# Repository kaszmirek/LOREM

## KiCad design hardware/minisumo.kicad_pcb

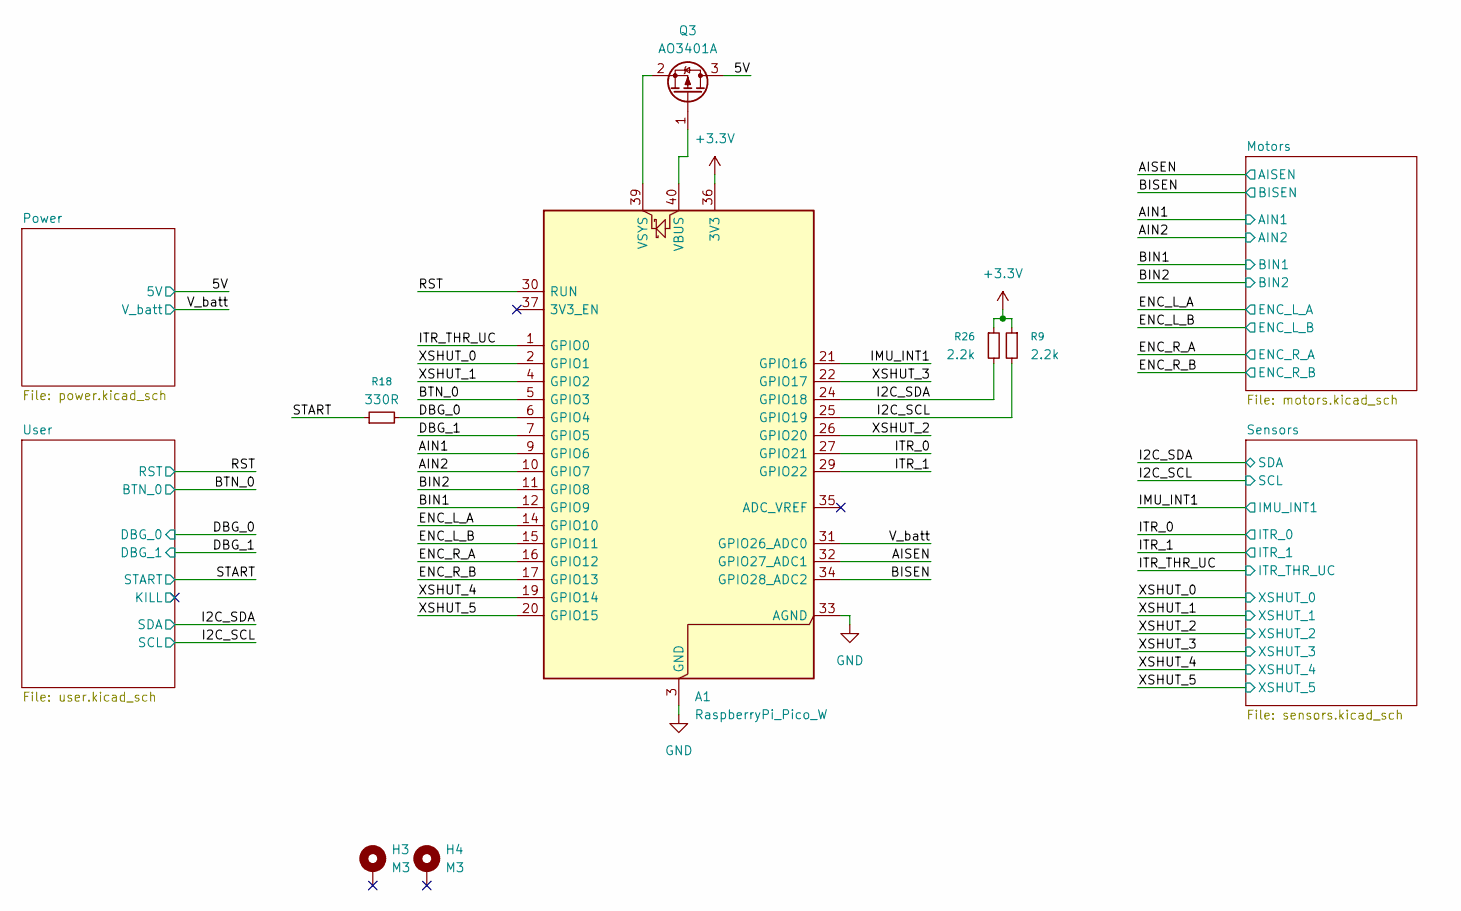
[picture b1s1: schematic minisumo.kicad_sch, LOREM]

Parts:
A1: RaspberryPi_Pico_W; RaspberryPi_Pico_W_SMD_HandSolder
H3, H4: M3; MountingHole_3.2mm_M3_Pad_Via
Q3: AO3401A; SOT-23
R9, R26: 2.2k; R_0402_1005Metric
R18: 330R; R_0402_1005Metric

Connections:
+3.3V: A1.36 (3V3), R9.1, R26.1; also elsewhere on the board
+5V: Q3.3 (D); also elsewhere on the board
/AIN1: A1.9 (GPIO6); also elsewhere on the board
/AIN2: A1.10 (GPIO7); also elsewhere on the board
/AISEN: A1.32 (GPIO27_ADC1); also elsewhere on the board
/BIN1: A1.12 (GPIO9); also elsewhere on the board
/BIN2: A1.11 (GPIO8); also elsewhere on the board
/BISEN: A1.34 (GPIO28_ADC2); also elsewhere on the board
/BTN_0: A1.5 (GPIO3); also elsewhere on the board
/DBG_0: A1.6 (GPIO4), R18.2; also elsewhere on the board
/DBG_1: A1.7 (GPIO5); also elsewhere on the board
/ENC_L_A: A1.14 (GPIO10); also elsewhere on the board
/ENC_L_B: A1.15 (GPIO11); also elsewhere on the board
/ENC_R_A: A1.16 (GPIO12); also elsewhere on the board
/ENC_R_B: A1.17 (GPIO13); also elsewhere on the board
/I2C_SCL: A1.25 (GPIO19), R9.2; also elsewhere on the board
/I2C_SDA: A1.24 (GPIO18), R26.2; also elsewhere on the board
/IMU_INT1: A1.21 (GPIO16); also elsewhere on the board
/ITR_0: A1.27 (GPIO21); also elsewhere on the board
/ITR_1: A1.29 (GPIO22); also elsewhere on the board
/ITR_THR_UC: A1.1 (GPIO0); also elsewhere on the board
/RST: A1.30 (RUN); also elsewhere on the board
/START: R18.1; also elsewhere on the board
/V_batt: A1.31 (GPIO26_ADC0); also elsewhere on the board
/XSHUT_0: A1.2 (GPIO1); also elsewhere on the board
/XSHUT_1: A1.4 (GPIO2); also elsewhere on the board
/XSHUT_2: A1.26 (GPIO20); also elsewhere on the board
/XSHUT_3: A1.22 (GPIO17); also elsewhere on the board
/XSHUT_4: A1.19 (GPIO14); also elsewhere on the board
/XSHUT_5: A1.20 (GPIO15); also elsewhere on the board
GND: A1.3 (GND), A1.8 (GND), A1.13 (GND), A1.18 (GND), A1.23 (GND), A1.28 (GND), A1.33 (AGND), A1.38 (GND); also elsewhere on the board
unnamed: A1.40 (VBUS), Q3.1 (G)
unnamed: A1.39 (VSYS), Q3.2 (S)

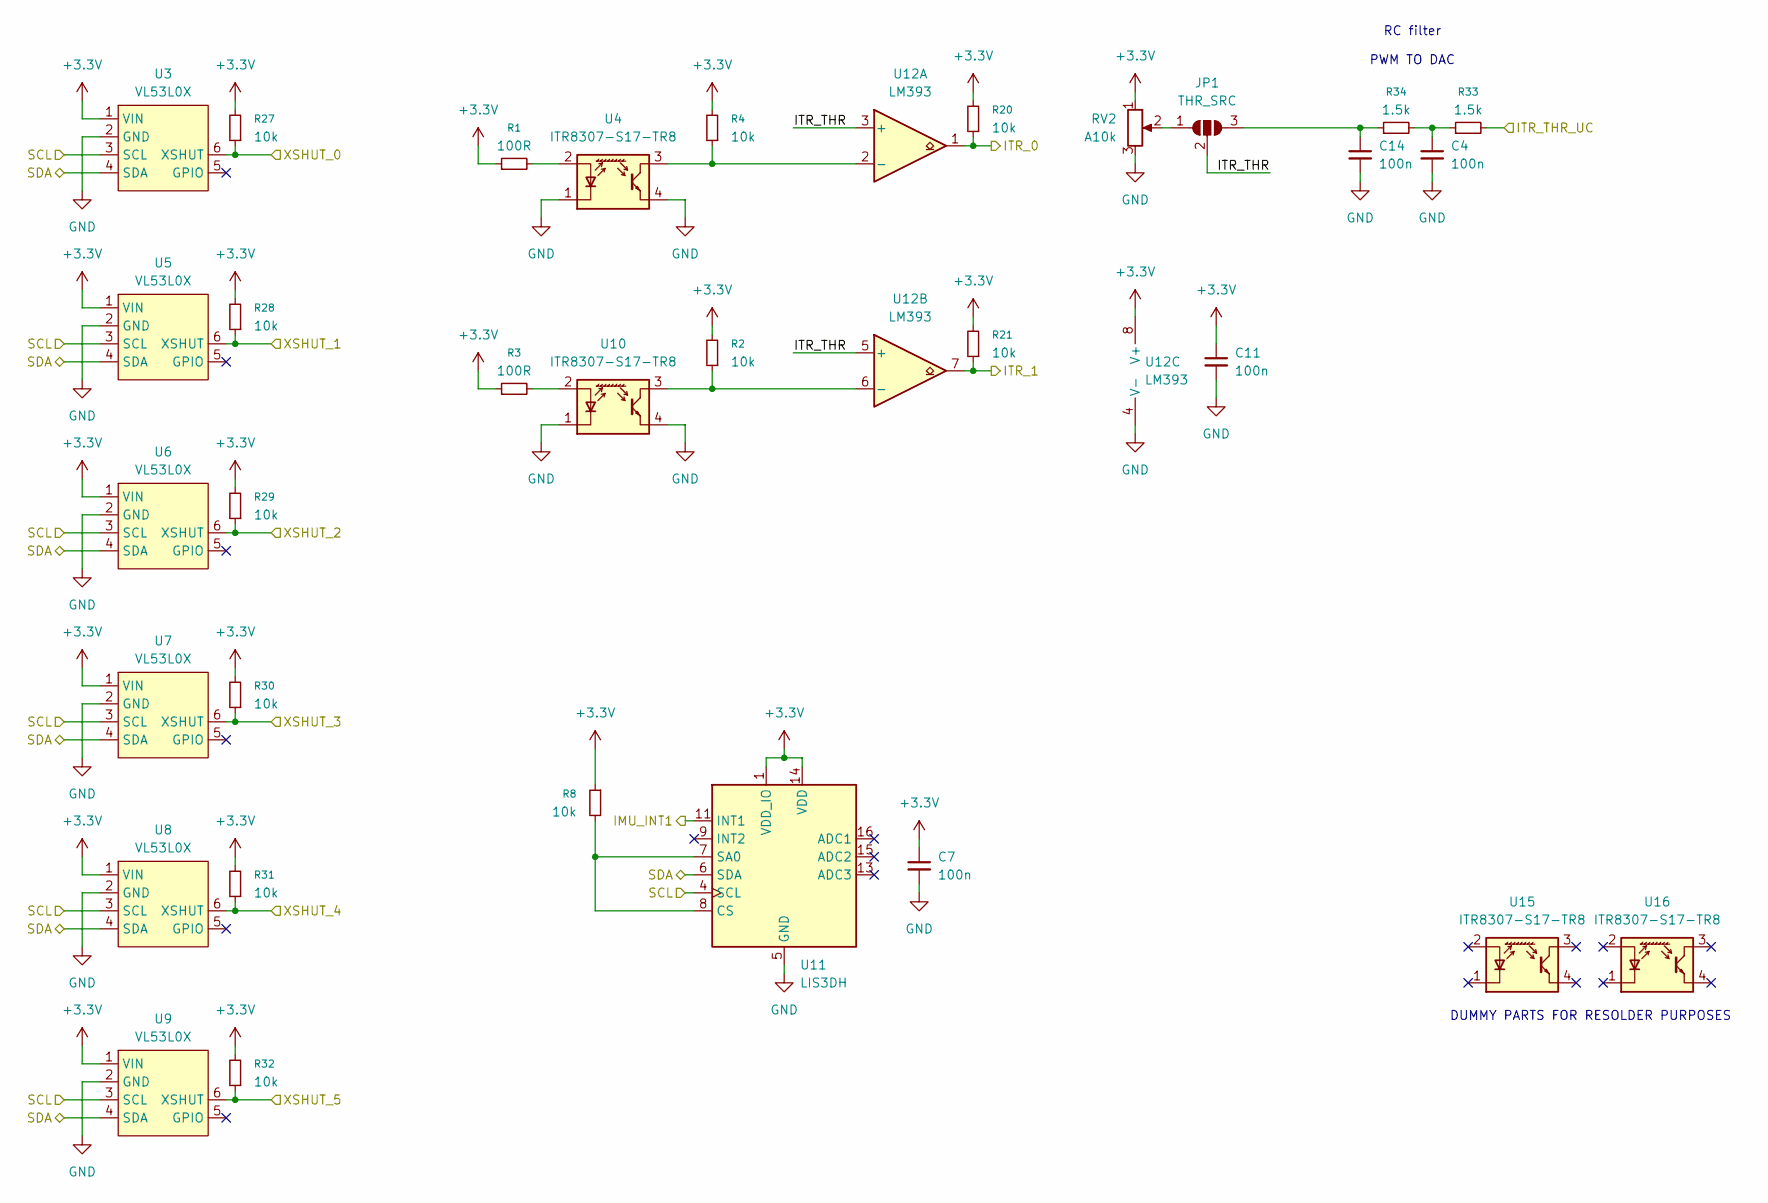
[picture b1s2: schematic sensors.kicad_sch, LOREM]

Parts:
C4, C7, C11, C14: 100n; C_0402_1005Metric
JP1: THR_SRC; SolderJumper-3_P1.3mm_Open_RoundedPad1.0x1.5mm_NumberLabels
R1, R3: 100R; R_0402_1005Metric
R2, R4, R8, R20, R21, R27, R28, R29, R30, R31, R32: 10k; R_0402_1005Metric
R33, R34: 1.5k; R_0402_1005Metric
RV2: A10k; Potentiometer_Vishay_T93YA_Vertical
U3, U5, U6, U7, U8, U9: VL53L0X
U4, U10, U15, U16: ITR8307-S17-TR8; Everlight_ITR1201SR10AR
U11: LIS3DH; LGA-16_3x3mm_P0.5mm_LayoutBorder3x5y
U12: LM393; SOIC-8_3.9x4.9mm_P1.27mm

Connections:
+3.3V: C7.1, C11.1, R1.1, R2.2, R3.1, R4.2, R8.1, R20.2, R21.2, R27.2, R28.2, R29.2, R30.2, R31.2, R32.2, RV2.1, U3.1 (VIN), U5.1 (VIN), U6.1 (VIN), U7.1 (VIN), U8.1 (VIN), U9.1 (VIN), U11.1 (VDD_IO), U11.14 (VDD), U12.8 (V+); also elsewhere on the board
/I2C_SCL: U3.3 (SCL), U5.3 (SCL), U6.3 (SCL), U7.3 (SCL), U8.3 (SCL), U9.3 (SCL), U11.4 (SCL); also elsewhere on the board
/I2C_SDA: U3.4 (SDA), U5.4 (SDA), U6.4 (SDA), U7.4 (SDA), U8.4 (SDA), U9.4 (SDA), U11.6 (SDA); also elsewhere on the board
/IMU_INT1: U11.11 (INT1); also elsewhere on the board
/ITR_0: R20.1, U12.1; also elsewhere on the board
/ITR_1: R21.1, U12.7; also elsewhere on the board
/ITR_THR_UC: R33.2; also elsewhere on the board
/Sensors/ITR_THR: JP1.2 (C), U12.3 (+), U12.5 (+)
/XSHUT_0: R27.1, U3.6 (XSHUT); also elsewhere on the board
/XSHUT_1: R28.1, U5.6 (XSHUT); also elsewhere on the board
/XSHUT_2: R29.1, U6.6 (XSHUT); also elsewhere on the board
/XSHUT_3: R30.1, U7.6 (XSHUT); also elsewhere on the board
/XSHUT_4: R31.1, U8.6 (XSHUT); also elsewhere on the board
/XSHUT_5: R32.1, U9.6 (XSHUT); also elsewhere on the board
GND: C4.2, C7.2, C11.2, C14.2, RV2.3, U3.2 (GND), U4.1 (K), U4.4, U5.2 (GND), U6.2 (GND), U7.2 (GND), U8.2 (GND), U9.2 (GND), U10.1 (K), U10.4, U11.5 (GND), U11.10 (GND), U11.12 (GND), U12.4 (V-); also elsewhere on the board
unnamed: C4.1, R33.1, R34.2
unnamed: JP1.1 (A), RV2.2
unnamed: C14.1, JP1.3 (B), R34.1
unnamed: R1.2, U4.2 (A)
unnamed: R3.2, U10.2 (A)
unnamed: R8.2, U11.7 (SA0), U11.8 (CS)
unnamed: R4.1, U4.3, U12.2 (-)
unnamed: R2.1, U10.3, U12.6 (-)

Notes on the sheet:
RC filter PWM TO DAC
DUMMY PARTS FOR RESOLDER PURPOSES

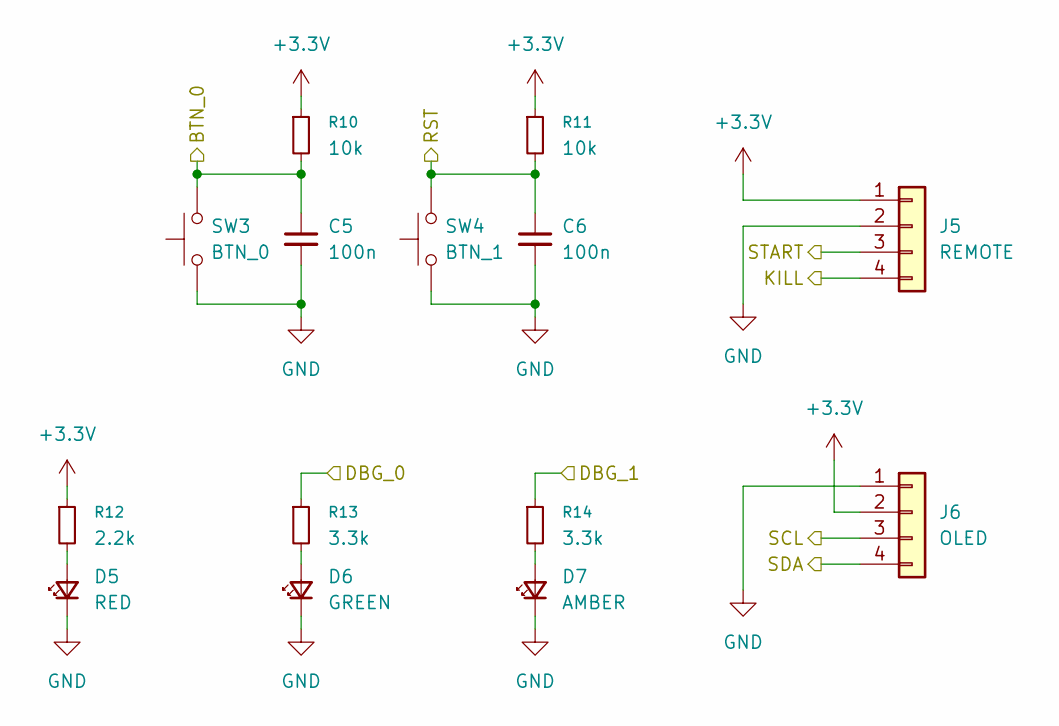
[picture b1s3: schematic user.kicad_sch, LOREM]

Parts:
C5, C6: 100n; C_0402_1005Metric
D5: RED; LED_0603_1608Metric
D6: GREEN; LED_0603_1608Metric
D7: AMBER; LED_0603_1608Metric
J5: REMOTE; PinHeader_1x04_P2.54mm_Vertical
J6: OLED; PinHeader_1x04_P2.54mm_Vertical
R10, R11: 10k; R_0402_1005Metric
R12: 2.2k; R_0402_1005Metric
R13, R14: 3.3k; R_0402_1005Metric
SW3: BTN_0; SW_SPST_TS-1088-xR020
SW4: BTN_1; SW_SPST_TS-1088-xR020

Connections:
+3.3V: J5.1, J6.2, R10.1, R11.1, R12.1; also elsewhere on the board
/BTN_0: C5.1, R10.2, SW3.2; also elsewhere on the board
/DBG_0: R13.1; also elsewhere on the board
/DBG_1: R14.1; also elsewhere on the board
/I2C_SCL: J6.3; also elsewhere on the board
/I2C_SDA: J6.4; also elsewhere on the board
/RST: C6.1, R11.2, SW4.2; also elsewhere on the board
/START: J5.3; also elsewhere on the board
/User/KILL: J5.4
GND: C5.2, C6.2, D5.1 (K), D6.1 (K), D7.1 (K), J5.2, J6.1, SW3.1, SW4.1; also elsewhere on the board
unnamed: D5.2 (A), R12.2
unnamed: D6.2 (A), R13.2
unnamed: D7.2 (A), R14.2

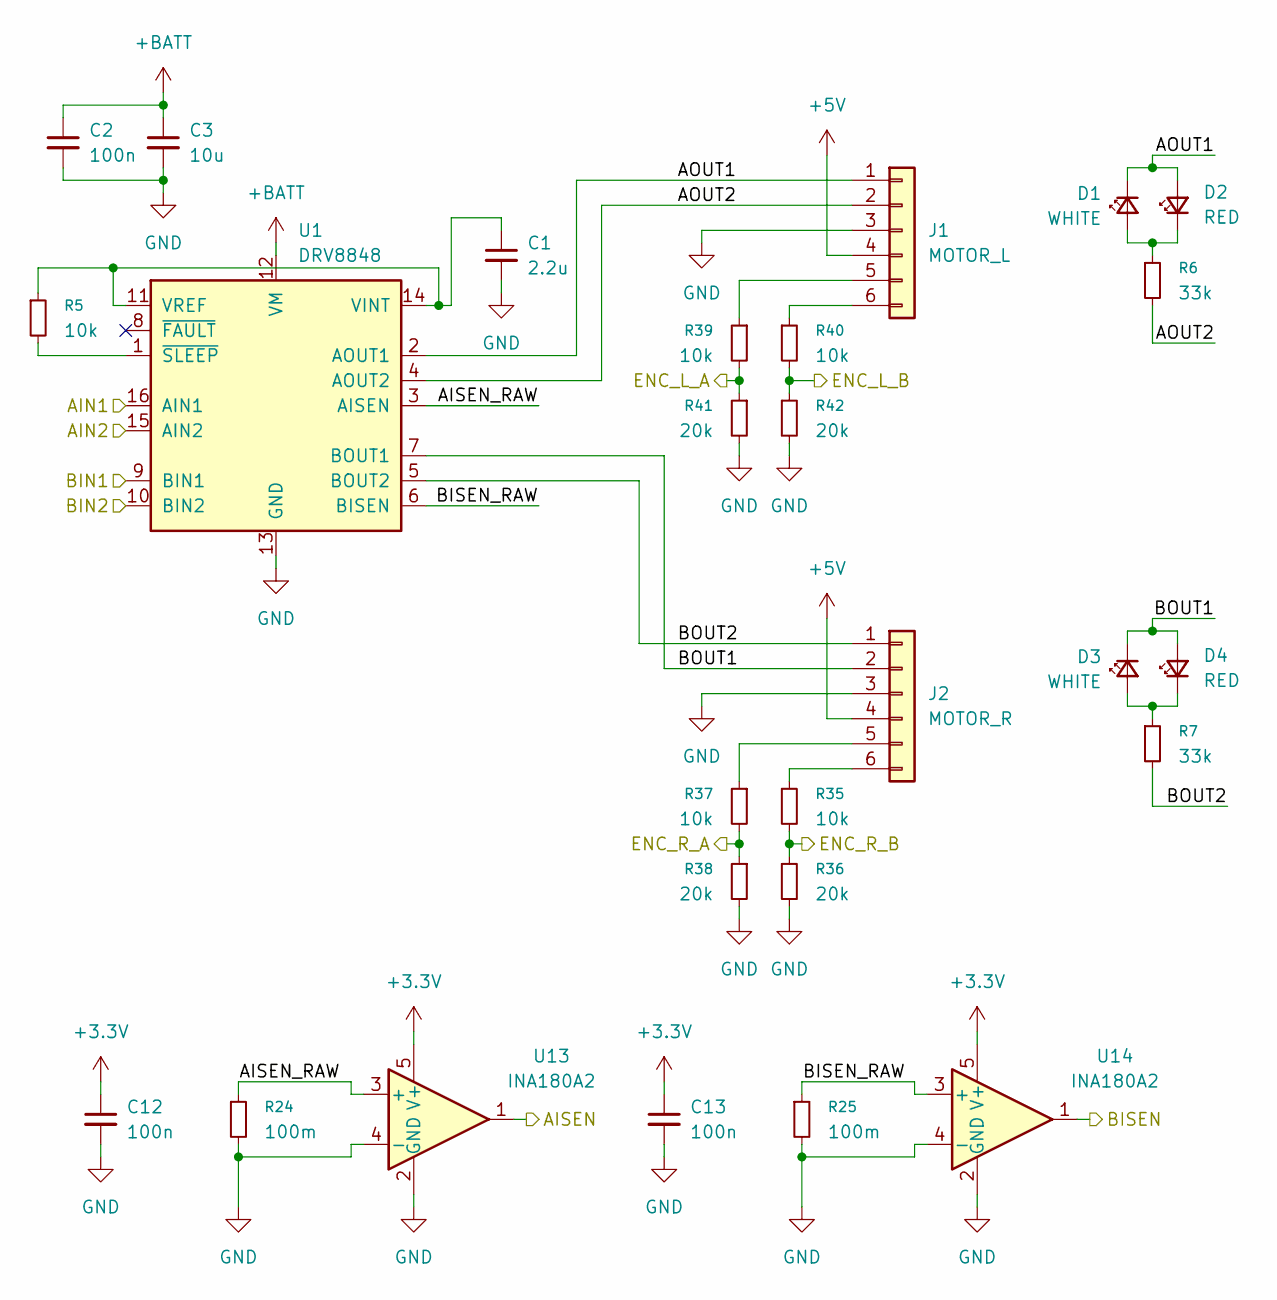
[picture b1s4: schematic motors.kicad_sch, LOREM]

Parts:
C1: 2.2u; C_0805_2012Metric
C2, C12, C13: 100n; C_0402_1005Metric
C3: 10u; C_0603_1608Metric
D1, D3: WHITE; LED_0603_1608Metric
D2, D4: RED; LED_0603_1608Metric
J1: MOTOR_L; IDC-Header_2x03_P2.54mm_Vertical
J2: MOTOR_R; IDC-Header_2x03_P2.54mm_Vertical
R5, R35, R37, R39, R40: 10k; R_0402_1005Metric
R6, R7: 33k; R_0402_1005Metric
R24, R25: 100m; R_1206_3216Metric
R36, R38, R41, R42: 20k; R_0402_1005Metric
U1: DRV8848; TSSOP-16-1EP_4.4x5mm_P0.65mm
U13, U14: INA180A2; SOT-23-5

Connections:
+3.3V: C12.1, C13.1, U13.5 (V+), U14.5 (V+); also elsewhere on the board
+5V: J1.4, J2.4; also elsewhere on the board
+BATT: C2.1, C3.1, U1.12 (VM); also elsewhere on the board
/AIN1: U1.16 (AIN1); also elsewhere on the board
/AIN2: U1.15 (AIN2); also elsewhere on the board
/AISEN: U13.1; also elsewhere on the board
/BIN1: U1.9 (BIN1); also elsewhere on the board
/BIN2: U1.10 (BIN2); also elsewhere on the board
/BISEN: U14.1; also elsewhere on the board
/ENC_L_A: R39.2, R41.1; also elsewhere on the board
/ENC_L_B: R40.2, R42.1; also elsewhere on the board
/ENC_R_A: R37.2, R38.1; also elsewhere on the board
/ENC_R_B: R35.2, R36.1; also elsewhere on the board
/Motors/AISEN_RAW: R24.1, U1.3 (AISEN), U13.3 (+)
/Motors/AOUT1: D1.1 (K), D2.2 (A), J1.1, U1.2 (AOUT1)
/Motors/AOUT2: J1.2, R6.2, U1.4 (AOUT2)
/Motors/BISEN_RAW: R25.1, U1.6 (BISEN), U14.3 (+)
/Motors/BOUT1: D3.1 (K), D4.2 (A), J2.2, U1.7 (BOUT1)
/Motors/BOUT2: J2.1, R7.2, U1.5 (BOUT2)
GND: C1.2, C2.2, C3.2, C12.2, C13.2, J1.3, J2.3, R24.2, R25.2, R36.2, R38.2, R41.2, R42.2, U1.13 (GND), U1.17 (GND), U13.2 (GND), U13.4 (-), U14.2 (GND), U14.4 (-); also elsewhere on the board
unnamed: D1.2 (A), D2.1 (K), R6.1
unnamed: D3.2 (A), D4.1 (K), R7.1
unnamed: J1.5, R39.1
unnamed: J1.6, R40.1
unnamed: J2.5, R37.1
unnamed: J2.6, R35.1
unnamed: C1.1, R5.1, U1.11 (VREF), U1.14 (VINT)
unnamed: R5.2, U1.1 (~SLEEP)

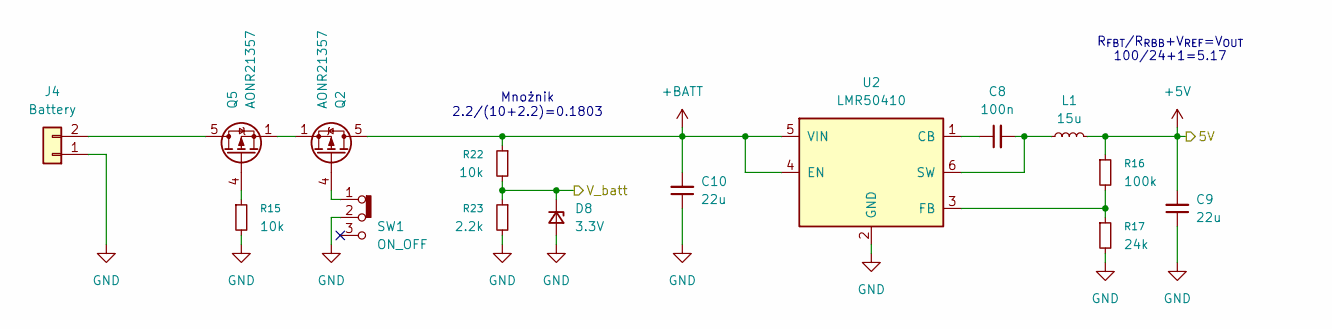
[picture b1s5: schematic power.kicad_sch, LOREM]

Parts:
C8: 100n; C_0603_1608Metric
C9, C10: 22u; C_0805_2012Metric
D8: 3.3V; D_SOD-523
J4: Battery; PinHeader_1x02_P2.54mm_Vertical
L1: 15u; L_APV_ANR5040
Q2, Q5: AONR21357; DFN_3.3x3.3
R15, R22: 10k; R_0402_1005Metric
R16: 100k; R_0402_1005Metric
R17: 24k; R_0402_1005Metric
R23: 2.2k; R_0402_1005Metric
SW1: ON_OFF; SW_Slide_SPDT_Straight_CK_OS102011MS2Q
U2: LMR50410; SOT-23-6

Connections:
+5V: C9.2, L1.2, R16.1; also elsewhere on the board
+BATT: C10.2, Q2.5 (D), R22.1, U2.4 (EN), U2.5 (VIN); also elsewhere on the board
/V_batt: D8.1 (K), R22.2, R23.1; also elsewhere on the board
GND: C9.1, C10.1, D8.2 (A), J4.1, R15.2, R17.2, R23.2, SW1.2 (B), U2.2 (GND); also elsewhere on the board
unnamed: J4.2, Q5.5 (D)
unnamed: Q2.4 (G), SW1.1 (A)
unnamed: Q2.1 (S), Q2.2 (S), Q2.3 (S), Q5.1 (S), Q5.2 (S), Q5.3 (S)
unnamed: Q5.4 (G), R15.1
unnamed: C8.1, U2.1 (CB)
unnamed: R16.2, R17.1, U2.3 (FB)
unnamed: C8.2, L1.1, U2.6 (SW)

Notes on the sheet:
R_{FBT}/R_{RBB}+V_{REF}=V_{OUT} 100/24+1=5.17
Mnożnik 2.2/(10+2.2)=0.1803

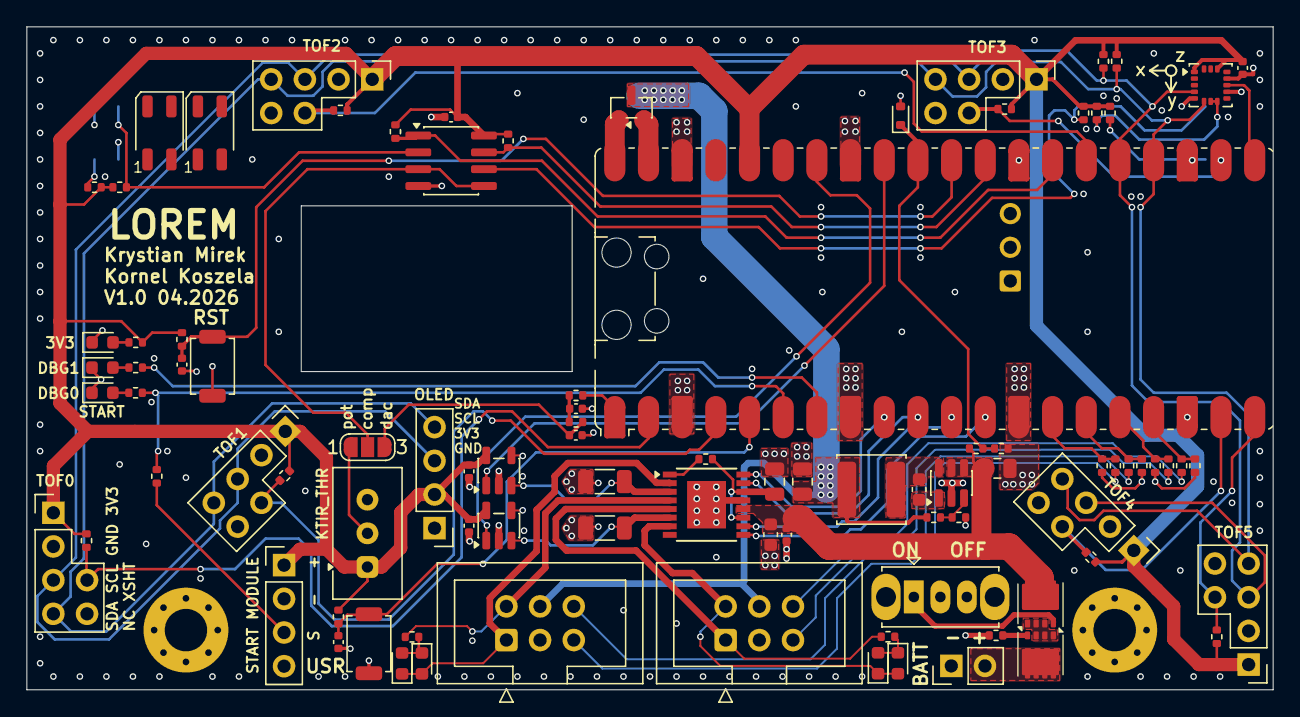
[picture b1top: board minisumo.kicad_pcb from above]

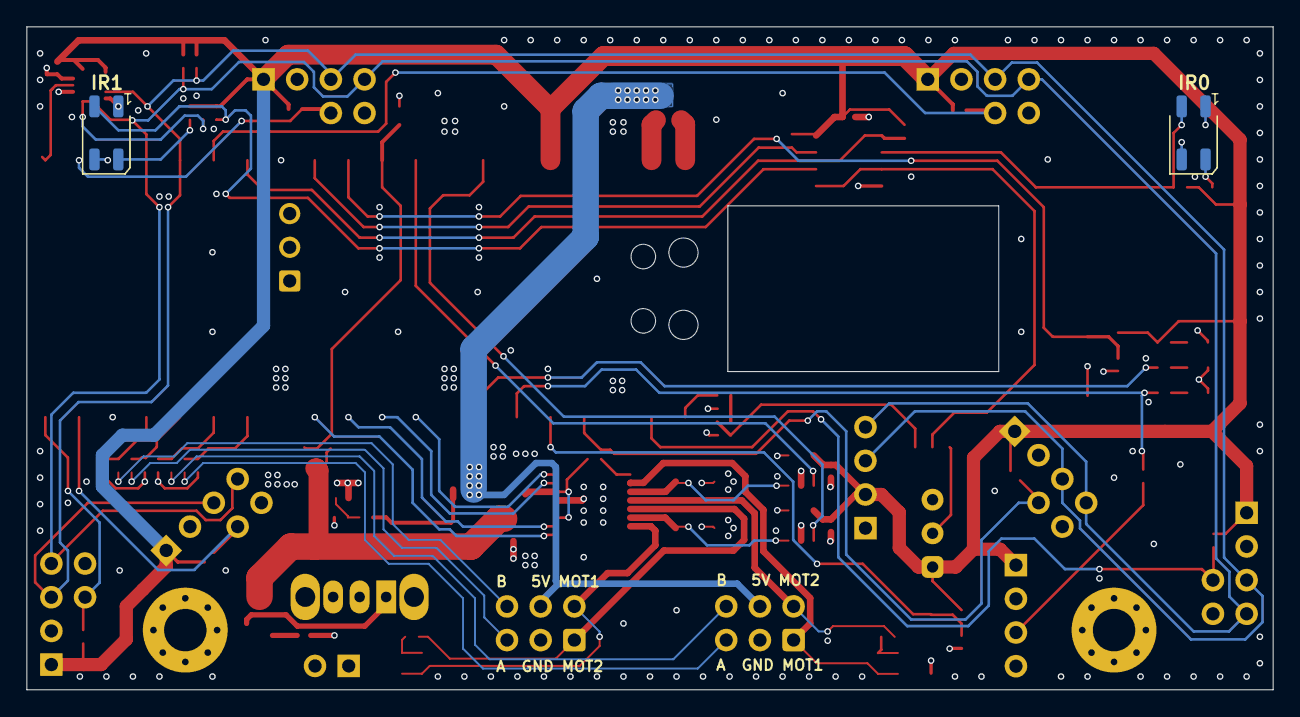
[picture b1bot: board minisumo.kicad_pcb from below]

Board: 4 copper layers, 94.0 x 50.0 mm, 96 parts (2 on the bottom side), 67 nets.

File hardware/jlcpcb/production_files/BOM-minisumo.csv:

Comment,Designator,Footprint,LCSC,Quantity
1.5k,"R33,R34",R_0402_1005Metric,C25867,2
100R,"R1,R3",R_0402_1005Metric,C25076,2
100k,R16,R_0402_1005Metric,C25741,1
100m,"R24,R25",R_1206_3216Metric,C25334,2
100n,C8,C_0603_1608Metric,C14663,1
100n,"C11,C12,C13,C14,C2,C4,C5,C6,C7",C_0402_1005Metric,C307331,9
10k,"R10,R11,R15,R2,R20,R21,R22,R27,R28,R29,R30,R31,R32,R35,R37,R39,R4,R40,R5,R8",R_0402_1005Metric,C25744,20
10u,C3,C_0603_1608Metric,C96446,1
15u,L1,L_APV_ANR5040,C167969,1
2.2k,"R12,R23,R26,R9",R_0402_1005Metric,C25879,4
2.2u,C1,C_0805_2012Metric,C377773,1
20k,"R36,R38,R41,R42",R_0402_1005Metric,C25765,4
22u,"C10,C9",C_0805_2012Metric,C45783,2
24k,R17,R_0402_1005Metric,C25769,1
3.3V,D8,D_SOD-523,C19077462,1
3.3k,"R13,R14",R_0402_1005Metric,C25890,2
330R,R18,R_0402_1005Metric,C25104,1
33k,"R6,R7",R_0402_1005Metric,C25779,2
AMBER,D7,LED_0603_1608Metric,C2296,1
AO3401A,Q3,SOT-23,C15127,1
AONR21357,"Q2,Q5",DFN_3.3x3.3,C431196,2
BTN_0,SW3,SW_SPST_TS-1088-xR020,C720477,1
BTN_1,SW4,SW_SPST_TS-1088-xR020,C720477,1
DRV8848,U1,TSSOP-16-1EP_4.4x5mm_P0.65mm,C131079,1
GREEN,D6,LED_0603_1608Metric,C2297,1
INA180A2,"U13,U14",SOT-23-5,C192764,2
ITR8307-S17-TR8,"U15,U16",Everlight_ITR1201SR10AR,C81632,2
LIS3DH,U11,LGA-16_3x3mm_P0.5mm_LayoutBorder3x5y,C15134,1
LM393,U12,SOIC-8_3.9x4.9mm_P1.27mm,C7955,1
LMR50410,U2,SOT-23-6,C2841056,1
RED,"D2,D4,D5",LED_0603_1608Metric,C2286,3
WHITE,"D1,D3",LED_0603_1608Metric,C2290,2

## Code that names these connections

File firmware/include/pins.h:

#pragma once

// --- Line sensor threshold (PWM out) ---
constexpr uint PIN_ITR_THR_UC   = 0;   // GPIO0 - OUT_PWM

// --- VL53L0X XSHUT pins (active low, ext. pull-up) ---
constexpr uint PIN_XSHUT_0      = 1;   // GPIO1
constexpr uint PIN_XSHUT_1      = 2;   // GPIO2
constexpr uint PIN_XSHUT_2      = 20;  // GPIO20
constexpr uint PIN_XSHUT_3      = 17;  // GPIO17
constexpr uint PIN_XSHUT_4      = 14;  // GPIO14
constexpr uint PIN_XSHUT_5      = 15;  // GPIO15

// --- User input ---
constexpr uint PIN_BTN_0        = 3;   // GPIO3  - IN, ext. pull-up, low when pressed
constexpr uint PIN_START        = 4;   // GPIO4  - IN/OUT, remote start active high / debug LED

// --- Debug LEDs ---
constexpr uint PIN_DBG_1        = 5;   // GPIO5  - OUT

// --- Motor control (DRV8833, int. pull-down) ---
constexpr uint PIN_AIN1         = 6;   // GPIO6  - OUT_PWM
constexpr uint PIN_AIN2         = 7;   // GPIO7  - OUT_PWM
constexpr uint PIN_BIN2         = 8;   // GPIO8  - OUT_PWM
constexpr uint PIN_BIN1         = 9;   // GPIO9  - OUT_PWM

// --- Encoders ---
constexpr uint PIN_ENC_L_A      = 10;  // GPIO10 - IN
constexpr uint PIN_ENC_L_B      = 11;  // GPIO11 - IN
constexpr uint PIN_ENC_R_A      = 12;  // GPIO12 - IN
constexpr uint PIN_ENC_R_B      = 13;  // GPIO13 - IN

// --- IMU ---
constexpr uint PIN_IMU_INT1     = 16;  // GPIO16 - IN, active high

// --- I2C (bus shared by VL53L0X, IMU) ---
constexpr uint PIN_I2C_SDA      = 18;  // GPIO18
constexpr uint PIN_I2C_SCL      = 19;  // GPIO19

// --- Line sensors (active low) ---
constexpr uint PIN_ITR0         = 21;  // GPIO21 - IN
constexpr uint PIN_ITR1         = 22;  // GPIO22 - IN

// --- ADC ---
// Multiplier: 0.1803 V/V  =>  V_batt = adc_voltage / 0.1803
constexpr uint PIN_V_BATT       = 26;  // ADC0
// Multiplier: 5 V/A  =>  I = adc_voltage / 5.0
constexpr uint PIN_AISEN        = 27;  // ADC1 - left motor current
constexpr uint PIN_BISEN        = 28;  // ADC2 - right motor current

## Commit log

2026-04-04 pcb and production files done
2026-04-06 ordered
2026-04-15 description table update
2026-04-16 motor holder
2026-04-22 feat: add build to gitignore
2026-04-22 feat: firwmare kuhwa
2026-04-24 fix: gpioput
2026-04-24 feat: PID
2026-04-24 ramp test
2026-04-24 feat: initial strat code
2026-04-24 fix: lsp shit
2026-04-24 fix: encoder on timre instead
2026-04-24 feat:watch
2026-04-24 feat: toggle btn
2026-04-24 fix: serial print
2026-04-24 fix: nicer display
2026-04-24 fix: adjust consts
2026-04-24 fix: nicetohaves
2026-04-24 Add picowota submodule
2026-04-24 fix: add ota
2026-04-24 fix: submodules
2026-04-25 chore: refactor
2026-04-25 feat: flashing
2026-04-25 fix: picosdk as submodule
2026-04-25 feat: debug program
2026-04-25 feat: imu
2026-04-25 fix: include imu shit in debug
2026-04-25 fix: submodule
2026-04-25 mhjghjghj
2026-04-25 fix: filtering
2026-04-25 fix:better filtering
2026-04-25 lmao czujniki
2026-04-25 lmao noa stratgia
